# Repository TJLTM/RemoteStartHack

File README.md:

# RemoteStartHack
When you can't remote start a PC with wake on lan or need to remotely snuff it with a pillow. This device goes inbetween the front panel power button and the Motherboard. It replicates pressing this button when WOL will not work for that computer (GIGABTYE I'M LOOKING AT YOU) 

This give youthe choice of using a Remote Relay that is wired into the system or an MCU that uses 5V to trigger a 5v Dip Relay. Example is using an Atmel 328P (arduino uno) I haven't tried using an ESP32/8266 with this since if a 5V source is used for the DIP-relay a 3.3v should be able to trigger the BJT and close the relay. 

GOing to work on a 3.3V version for this possibly ESP based.

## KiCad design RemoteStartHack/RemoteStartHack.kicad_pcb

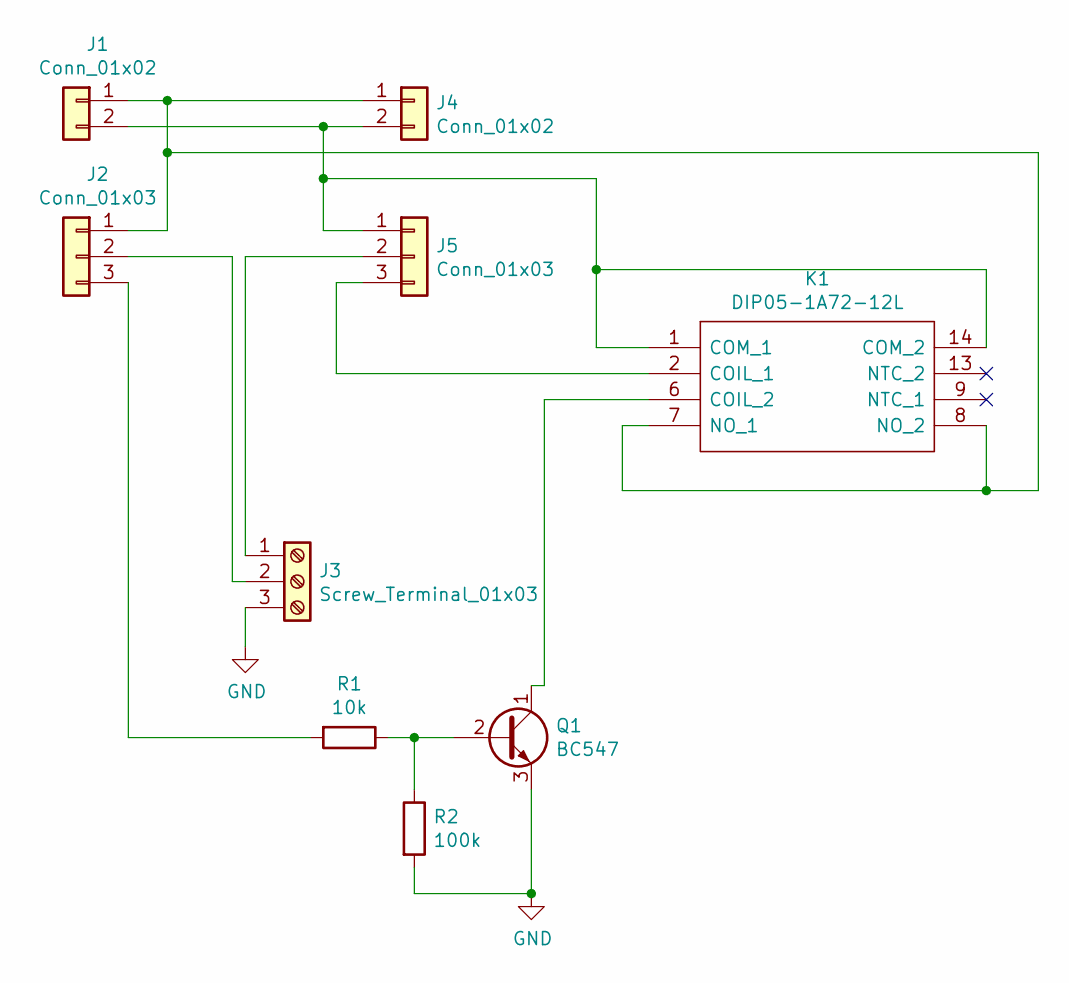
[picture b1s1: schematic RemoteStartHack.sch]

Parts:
J1, J4: Conn_01x02; PinHeader_1x02_P2.54mm_Horizontal
J2, J5: Conn_01x03; PinHeader_1x03_P2.54mm_Vertical
J3: Screw_Terminal_01x03; TerminalBlock_Phoenix_MKDS-1,5-3-5.08_1x03_P5.08mm_Horizont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
K1: DIP05-1A72-12L; DIP051A7212L; Mouser Part Number 876-DIP05-1A72-12L
Q1: BC547; TO-92_Inline
R1: 10k; R_Axial_DIN0207_L6.3mm_D2.5mm_P10.16mm_Horizontal
R2: 100k; R_Axial_DIN0207_L6.3mm_D2.5mm_P10.16mm_Horizontal

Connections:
GND: J3.3, Q1.3 (E), R2.2
unnamed: J1.1, J2.1, J4.1, K1.7 (NO_1), K1.8 (NO_2)
unnamed: J1.2, J4.2, J5.1, K1.1 (COM_1), K1.14 (COM_2)
unnamed: J2.2, J3.2
unnamed: J2.3, R1.2
unnamed: J3.1, J5.2
unnamed: J5.3, K1.2 (COIL_1)
unnamed: K1.6 (COIL_2), Q1.1 (C)
unnamed: Q1.2 (B), R1.1, R2.1

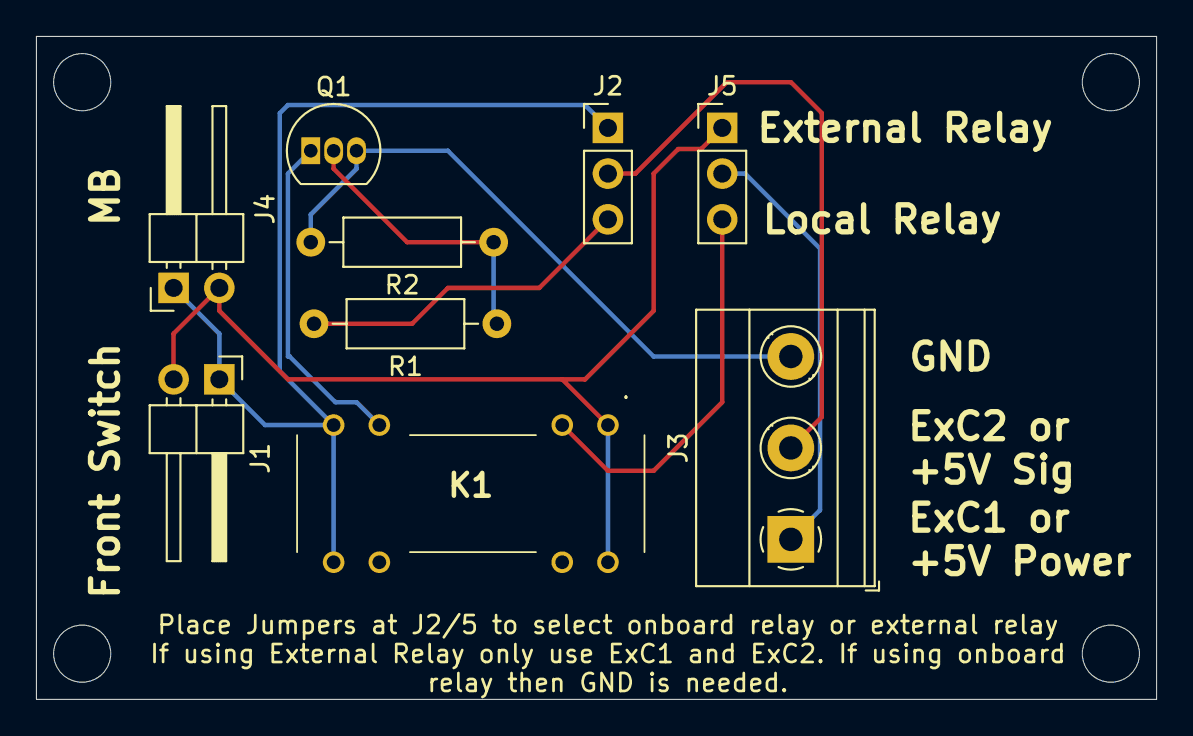
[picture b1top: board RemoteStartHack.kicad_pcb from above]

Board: 2 copper layers, 62.2 x 36.8 mm, 9 parts (0 on the bottom side), 9 nets.

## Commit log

2021-09-14 initial
2021-09-14 Fab Files for Version 0.1
2021-09-16 output file update
2021-10-08 Create LICENSE
2021-10-13 splitting this into a 5v and 3.3v version possibly ESP based.
2021-10-25 case stuff.
2021-10-26 adding a model with mounting ears and added .02 inches to the studs for holding the board.
2021-11-02 adding a photo
